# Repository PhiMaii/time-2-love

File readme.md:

---

# ❤️ Time2Love — Connected Countdown Device

**Time2Love** is a small, WiFi-connected countdown device built with an ESP8266 and an OLED display.  
It shows the remaining time until a meaningful event (e.g. the next time two people see each other) and allows two paired devices to communicate through a simple server — including a remote “blink” signal.

---

## TO-DOs

- [ ] Server/Backend improvements:
  - [ ] Make a more fancy server using NEXT.js
  - [ ] Implement a custom DIY OTA server
  - [ ] latency and uptime/online charts on dashboard
  
- [ ] Hardware improvements
  - [ ] ...
  
- [ ] Future feature ideas:
  - [ ] use Websockets for instant blink responses
  - [ ] Devices send heartbeats to track online status from the dashboard
  - [ ] remote configuration (and management) of the devices 

---

## Key features

- Countdown to a fixed event date (weeks / days / hours / minutes)
- WiFi-connected event synching
- 128×32 OLED display (SSD1306, U8g2)
- 2 physical buttons to trigger a remote blink and toggle sleep
- Remote blink when the paired device presses its button
- Simple Node.js server for pairing & messaging
- Persistent configuration via **EEPROM**
- OTA firmware updates via **OTAdrive**

---

## Required hardware

- Wemos D1 Mini (ESP8266) or compatible clone
- 128×32 OLED display (SSD1306, I2C)
- 2 Push buttons
- WS2812B adressable RGB LEDs
- (Optional: 3D printed case) 

---

## 📁 Project Structure

```
├── esp_client/                         # ESP8266 firmware (Wemos D1 Mini)
│   ├── build/                          # Arduino build output (auto-generated)
│   │   └── esp8266.esp8266_d1_mini_clone/
│   │       ├── esp_client.ino.elf      # 
│   │       ├── esp_client.ino.map      # 
│   │       └── firmware.bin            # Final firmware image (used for OTA)
│   │
│   ├── esp_client.ino                  # Main Arduino entry point (setup & loop)
│   ├── Config.h                        # Global configuration (WiFi, server URL, OTAdrive API key)
│   │
│   ├── ButtonHandler.h                 # Button press and hold handling and event triggering
│   ├── ButtonHandler.cpp               # 
│   │
│   ├── DisplayManager.h                # Display rendering, icons, countdown and blink visualization
│   ├── DisplayManager.cpp              # 
│   │
│   ├── EEPROMManager.h                 # EEPROM initialization, read/write logic, defaults handling
│   ├── EEPROMManager.cpp               # 
│   │
│   ├── EventClock.h                    # Time calculation (weeks / days / hours / minutes) and server sync
│   ├── EventClock.cpp                  # 
│   │
│   ├── WiFiManager.h                   # WiFi setup and connection
│   ├── WiFiManager.cpp                 #
│   │
│   ├── ServerClient.h                  # Device registration, peer handling, blink messaging via HTTP
│   ├── ServerClient.cpp                #
│   │
│   ├── LEDManager.h                    # Initialization and controlling of the LEDs
│   ├── LEDManager.cpp                  #
│   │
│   ├── BootManager.h                   # Startup sequence and display boot progress
│   ├── BootManager.cpp                 #
│   │
│   ├── DelayedCaller.h                 # Helper to delay a function call by a variable amount
│   ├── DelayedCaller.cpp               #
│   │
│   ├── OTAManager.h                    # OTA initialization, periodic update checks, reboot handling
│   └── OTAManager.cpp                  # 
│
├── server/                             # Simple Node.js backend server
│   ├── Dockerfile                      # Creates the docker container thats used to run the server
│   ├── entrypoint.sh                   # Used by the local GitHub runner to pull the latest changes from GitHub
│   ├── server.js                       # Express server handles: event date, device pairing, blink events
│   ├── package.json                    # Node.js dependencies and scripts
│   └── package-lock.json               # Locked dependency versions
│
└── README.md                           # Project documentation
```

---

## Architecture Overview

### ESP Device
- Connects to WiFi
- Registers itself at the server using a persistent `DEVICE_ID`
- Fetches a fixed event timestamp from the server
- Checks for newer firmware versions
- Displays remaining time to the event
- Polls for blink events periodically
- Sends blink triggers on button press

### Server
- Keeps an in-memory list of registered devices
- Returns peer devices
- Stores blink events temporarily
- Provides a hard-coded event date

---

## 💾 EEPROM Usage

The EEPROM is used for **persistent configuration**:

| Name        | Description                    | Start Addr | Length |
|-----------|--------------------------------|---------|-----|
| Magic bit | Shows if the EEPROM has been written to before   |0|1|
| Device ID   | Unique device ID       |1|32|
|SF Version| The current firmware version of the device|33|32|
|SSID|SSID of a stored WiFi network | 65| 32|
|WiFi Password| Password for the stored WiFi network | 97|64|

EEPROM is initialized on first boot and reused on every restart.
Total EEPROM size is 256.

---

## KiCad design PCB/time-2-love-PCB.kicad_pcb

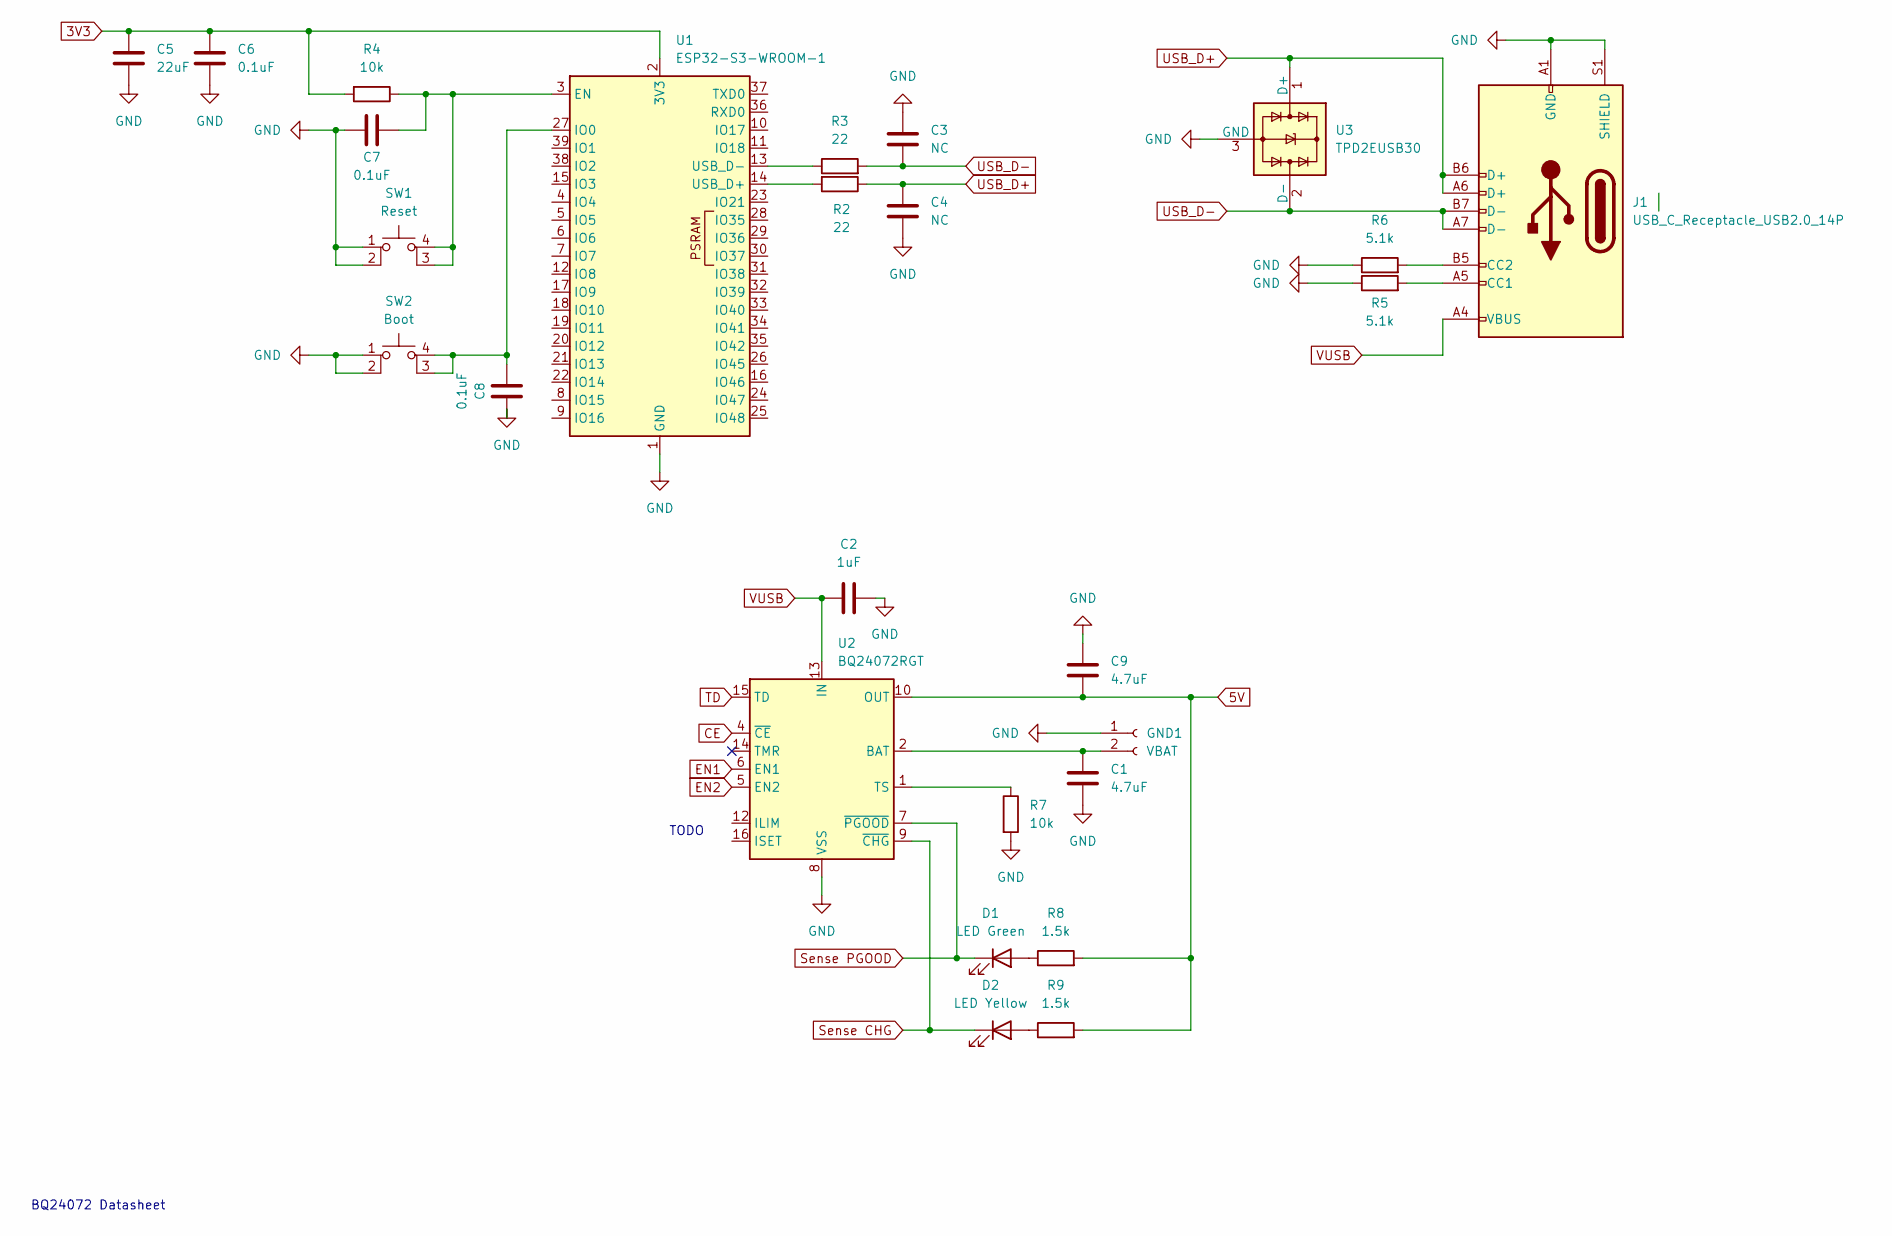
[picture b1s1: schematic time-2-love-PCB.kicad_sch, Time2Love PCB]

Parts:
C1, C9: 4.7uF; C_0603_1608Metric
C2: 1uF; C_0603_1608Metric
C3, C4: NC; C_0603_1608Metric
C5: 22uF; C_0603_1608Metric
C6, C7, C8: 0.1uF; C_0603_1608Metric
D1: LED Green; LED_0603_1608Metric
D2: LED Yellow; LED_0603_1608Metric
GND1: VBAT; JST_PH_S2B-PH-K_1x02_P2.00mm_Horizontal
J1: USB_C_Receptacle_USB2.0_14P
R2, R3: 22; R_0603_1608Metric
R4, R7: 10k; R_0603_1608Metric
R5, R6: 5.1k; R_0603_1608Metric
R8, R9: 1.5k; R_0603_1608Metric
SW1: Reset; SW_MEC_5GSH9
SW2: Boot; SW_MEC_5GSH9
U1: ESP32-S3-WROOM-1
U2: BQ24072RGT; VQFN-16-1EP_3x3mm_P0.5mm_EP1.6x1.6mm
U3: TPD2EUSB30; Texas_DRT-3

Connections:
3V3: C5.2, C6.2, R4.2, U1.2 (3V3)
5V: C9.2, R8.2, R9.2, U2.10 (OUT), U2.11 (OUT)
CE: U2.4 (~CE)
EN1: U2.6 (EN1)
EN2: U2.5 (EN2)
GND: C1.2, C2.2, C3.2, C4.1, C5.1, C6.1, C7.2, C8.1, C9.1, GND1.1, J1.A1 (GND), J1.A12 (GND), J1.B1 (GND), J1.B12 (GND), J1.S1 (SHIELD), R5.1, R6.1, R7.2, SW1.1, SW1.2, SW2.1, SW2.2, U1.1 (GND), U1.40 (GND), U1.41 (GND), U2.8 (VSS), U2.17 (VSS), U3.3 (GND)
unnamed: D1.2 (A), R8.1
unnamed: D2.2 (A), R9.1
unnamed: C1.1, GND1.2, U2.2 (BAT), U2.3 (BAT)
unnamed: J1.A5 (CC1), R5.2
unnamed: J1.B5 (CC2), R6.2
unnamed: C7.1, R4.1, SW1.3 (K), SW1.4 (A), U1.3 (EN)
unnamed: C8.2, SW2.3 (K), SW2.4 (A), U1.27 (IO0)
unnamed: R2.2, U1.14 (USB_D+)
unnamed: R3.1, U1.13 (USB_D-)
unnamed: R7.1, U2.1 (TS)
Sense CHG: D2.1 (K), U2.9 (~CHG)
Sense PGOOD: D1.1 (K), U2.7 (~PGOOD)
TD: U2.15 (TD)
USB_D+: C4.2, J1.A6 (D+), J1.B6 (D+), R2.1, U3.1 (D+)
USB_D-: C3.1, J1.A7 (D-), J1.B7 (D-), R3.2, U3.2 (D-)
VUSB: C2.1, J1.A4 (VBUS), J1.A9 (VBUS), J1.B4 (VBUS), J1.B9 (VBUS), U2.13 (IN)

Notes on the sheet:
BQ24072 Datasheet
TODO

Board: 2 copper layers, 25 parts (0 on the bottom side), 16 nets, no tracks yet.

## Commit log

2025-12-12 Added automatic build action
2025-12-12 First working version
2025-12-12 Moved DeviceID and SoftwareVersion to EEPROM
2025-12-12 General improvements
2025-12-12 Reworked styling of signal-strength-indicators and fixed server status indicator
2025-12-12 Updated workflow to automatically build a .bin file
2025-12-12 Fixed workflow
2025-12-12 Updated workflow
2025-12-12 Upgrade Arduino CLI setup action to version 2
2025-12-12 Reorganised file structure to create a valid .ino project
2025-12-12 Rename compile step for ESP8266 D1 mini sketch
2025-12-12 Refactor build workflow by removing unnecessary steps
    Removed configuration steps for Sketchbook and verification.
2025-12-12 Add U8g2 library installation step to build workflow
2025-12-12 Modify version file creation in build workflow
    Updated version file creation step in workflow.
2025-12-12 Fix formatting and update version output in build.yml
2025-12-12 Made text positioning adaptive
2025-12-12 Small UI improvements and fixes
2025-12-12 Add production branch to build workflow
2025-12-12 Rename binary to firmware.bin in build workflow
    Add step to rename the binary after build
2025-12-12 Working version
2025-12-12 Simplify rename binary step in build workflow
2025-12-12 Modify build workflow for production branch
    Updated build workflow to trigger on production branch and added step to rename binary.
2025-12-12 Remove binary renaming step from build workflow
    Removed the step to rename the binary file in the build process.
2025-12-13 Added readme file
2025-12-13 Working build action
2025-12-13 Removed useless buiild directory
2025-12-13 Refactored EEPROM manager to be more adaptive and versatile
2025-12-13 Working communication with OTAdrive servers
2025-12-13 First prototype of OTA with progress display
2025-12-13 Recompiled .bin
2025-12-13 Add README.md with project overview, features, hardware requirements, and architecture details
2025-12-13 Add TO-DOs section to README.md for future development tasks
2025-12-14 Formatted all the code correctly
2025-12-14 Reworked DisplayManager and implemented a better state logic
2025-12-14 Working check-for-update logic and version comparing
2025-12-14 Recompiled firmware version 0.1.2
2025-12-14 Working OTA updates
2025-12-14 Reworked EEPROM manager to make more efficient and reusable
2025-12-14 Working Wifi manager to enter wifi credentials
2025-12-14 Fully working Wifi manager
2025-12-14 Refactor README for clarity and conciseness
    Removed sections on OTA firmware updates and optional hardware requirements. Updated EEPROM usage table for clarity.
2025-12-15 Cleaned up and reorganised the codebase
2025-12-15 Refactored codebase
2025-12-15 Fixed merge errors
2025-12-15 Refactor button handling in esp_client.ino to use separate blink and sleep buttons; add drawSleep function in DisplayManager for sleep state display.
2025-12-15 Add LEDManager for heartbeat LED control; integrate into esp_client.ino
2025-12-15 Add installation steps for additional libraries
2025-12-15 Preparation for automatic firmware build
2025-12-15 Add render configuration definitions for display frame rate and main loop delay
2025-12-15 Update display refresh rate condition in updateDisplay method
2025-12-15 Update EEPROM default values and adjust main loop delay
2025-12-15 Update number of LEDs from 3 to 8 in configuration
2025-12-15 Implement BootManager and DisplayManager integration for boot progress display
2025-12-15 Add cad and pcb directories
2025-12-15 Enhance ButtonHandler to support long press detection
2025-12-15 Enhance captive portal HTML for WiFi setup with improved styling and user experience
2025-12-15 update display logic; add Icons header for update icon
2025-12-16 Recompiled firmware version 0.2.1
2025-12-16 Add DelayedCaller class for scheduling function calls with delay
2025-12-16 Refactor ButtonHandler for improved long press detection and debounce logic
2025-12-16 Working OTA updates triggered by long pressing the sleep button
2025-12-16 Add deployment workflow and Docker setup for blink-server
2025-12-16 Update EVENT_EPOCH to reflect new event date
2025-12-16 Revise README for clarity and additional details
    Updated README with new features, hardware requirements, and project structure.
2025-12-16 Update .gitignore to include additional file patterns for better exclusion
2025-12-16 Update display behavior and EEPROM device ID for improved functionality
2025-12-16 Add KiCad PCB and schematic files
2025-12-19 Decided on an ESP 32 C3 WROOM 02 as mcu
2025-12-25 Updated .gitignore
2025-12-25 Updated Server to use MQTT
2025-12-28 Update .gitignore to include additional ignored files and folders
2025-12-28 Add server/node_modules to .gitignore
2025-12-28 mqtt server v1
2025-12-28 Add server configuration and device management for MQTT and push notifications
2025-12-28 Working push notifications on button press
2025-12-28 Updated .gitignore to include PCB files
2025-12-28 Added some components to the scematic
2025-12-28 Deleted node_modules
2025-12-28 Renamed old server files
2025-12-28 Changed the style and icon of the PWA
2025-12-28 Updated .gitignore to include PWA Push secrets
2025-12-28 Documented and cleaned up the codebase
2025-12-29 Implemented a /health route to check it the server adress is valid
2025-12-29 Documented the type of device
2025-12-29 Example device config file
2025-12-29 Uploaded icons for the PWA
2025-12-29 Planned the MQTT topic sturcture
2025-12-29 Moved image file to the correct folder
2025-12-29 Cleanded up the website and added styling
2025-12-30 Made it possible to set the event timestamp via the website and store it to a json file
2025-12-30 Updated the npm start command to work correctly
2025-12-31 Added a new MQTT topic
2025-12-31 Added a '/ota' route to upload new firmware image
2025-12-31 Added local .json files to be ignored
2025-12-31 Updated .gitignore to include PlatformIO files
2026-01-02 Added new client based on PlatformIO as a submodule and moved old version using Arduino IDE to a new folder
2026-01-02 Updaetd the .gitmodules file to fix the path
2026-01-02 Added new client version as a submodule to the git repo
2026-01-02 Added the react-native Expo app as submodule
